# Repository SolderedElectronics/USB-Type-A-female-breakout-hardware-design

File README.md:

# USB Type A female breakout Hardware Design

## About the Product

|  |
| :----------------------------------------------------------: |
| [Buy USB Type A female breakout](https://www.solde.red/333132) |

The USB Type-A connection is still prevalent. If it’s in the electronic devices everywhere around us, it is only natural that we’d want it in our electronic projects. Adding a USB Type-A connection to your circuit is as easy as pie with this breakout board.

The breakout board breaks the GND, D+, D-, and VUSB pins out to the plated through-holes.

---

## Repository Contents

This repository contains all design files for USB Type A female breakout, organized as follows:

- **`CAD` folder**: Contains KiCAD design files, including:
  - Schematics
  - PCB layout
  - Panel PCB layout
  - Source 3D files in Fusion360, if any
  - All files are sorted by version with a detailed change log.
- **`OUTPUTS` folder**: Includes all production-ready files, such as:
  - Bill of Materials (BOM) and interactive BOM (iBOM)
  - PDF versions of schematics
  - 3D `.step` file of the board
  - 3D-printable models
  - Gerber files for PCB manufacturing
  - Image of the pinout of the board
  - Product image
  - Compliance, legal and generic sales documents

Refer to the `Change Log` in the CAD folder for details about updates between versions.

---

## Learn More About the Product

Beyond the repository, explore the following resources:

### Soldered Verify

The **Soldered Verify** system ensures every board you purchase from Soldered is fully functional. It also provides access to exclusive test data for your product. To get started, find the unique Soldered Verify ID on your product's packaging and enter the ID on the [Soldered Verify page](https://soldered.com/verify/) to access test results and additional product details.

### Soldered Community

Soldered Community is your go-to place for technical support. Our engineers track and answer all questions posted there, and it’s a great space for the maker community. Get answers to your questions and solutions for your challenges at [Soldered Community](https://soldered.com/community).

### solde.red

solde.red is an ultimate URL shortener and information hub. Access it by typing solde.red/ followed by your product SKU, e.g., [solde.red/333000](https://solde.red/333000), to find getting-started guides, datasheets, open-source hardware and software files, certifications, images, pinouts, and more. Read more about the shortener [here](https://solde.red/info/).

---

## Contributing

Contributions are welcome! Here’s how you can get involved:

- Submit pull requests to enhance the design or fix issues.
- Report bugs or problems by opening an issue.

We encourage community collaboration to make this product even better.

---

## About Soldered

[Soldered for Makers](https://soldered.com) specializes in designing and manufacturing electronic products tailored for enthusiasts, ranging from hobbyists to professionals. Our portfolio includes electronic boards, sensors, and actuators that are widely utilized in fields such as microelectronics, mechatronics, robotics, programming, and IoT. Every product we offer is designed in-house and built upon open-source hardware and software platforms. Proudly certified and manufactured within the European Union, our catalog likely includes the product you need for your project.

We complement these products with comprehensive tutorials and manuals, product descriptions, schematics, programming codes, and project examples. Our round-the-clock [customer and technical support](https://soldered.com/community) is available for all our products, irrespective of the sales channel. Soldered’s success and services reflect our maker community’s unwavering [trust](https://www.trustpilot.com/review/soldered.com), for which we are deeply grateful. Join our community and create using Soldered products.

---

## License

All Soldered open-source hardware (OSH) is under The TAPR Open Hardware License. Read more in the LICENSE file located in this repository.

**Disclaimer:**

No warranty - all designs in this repository are distributed in the hope that they will be useful, but without any warranty. They are provided "AS IS", therefore without warranty of any kind, either expressed or implied. The entire quality and performance of what you do with the contents of this repository are your responsibility. In no event Soldered Electronics will be liable for your damages, or losses, including any general, special, incidental, or consequential damage arising out of the use or inability to use the contents of this repository. 

---

## Have fun!

Thank you for your support from your fellow makers at Soldered Electronics.

Happy Making!

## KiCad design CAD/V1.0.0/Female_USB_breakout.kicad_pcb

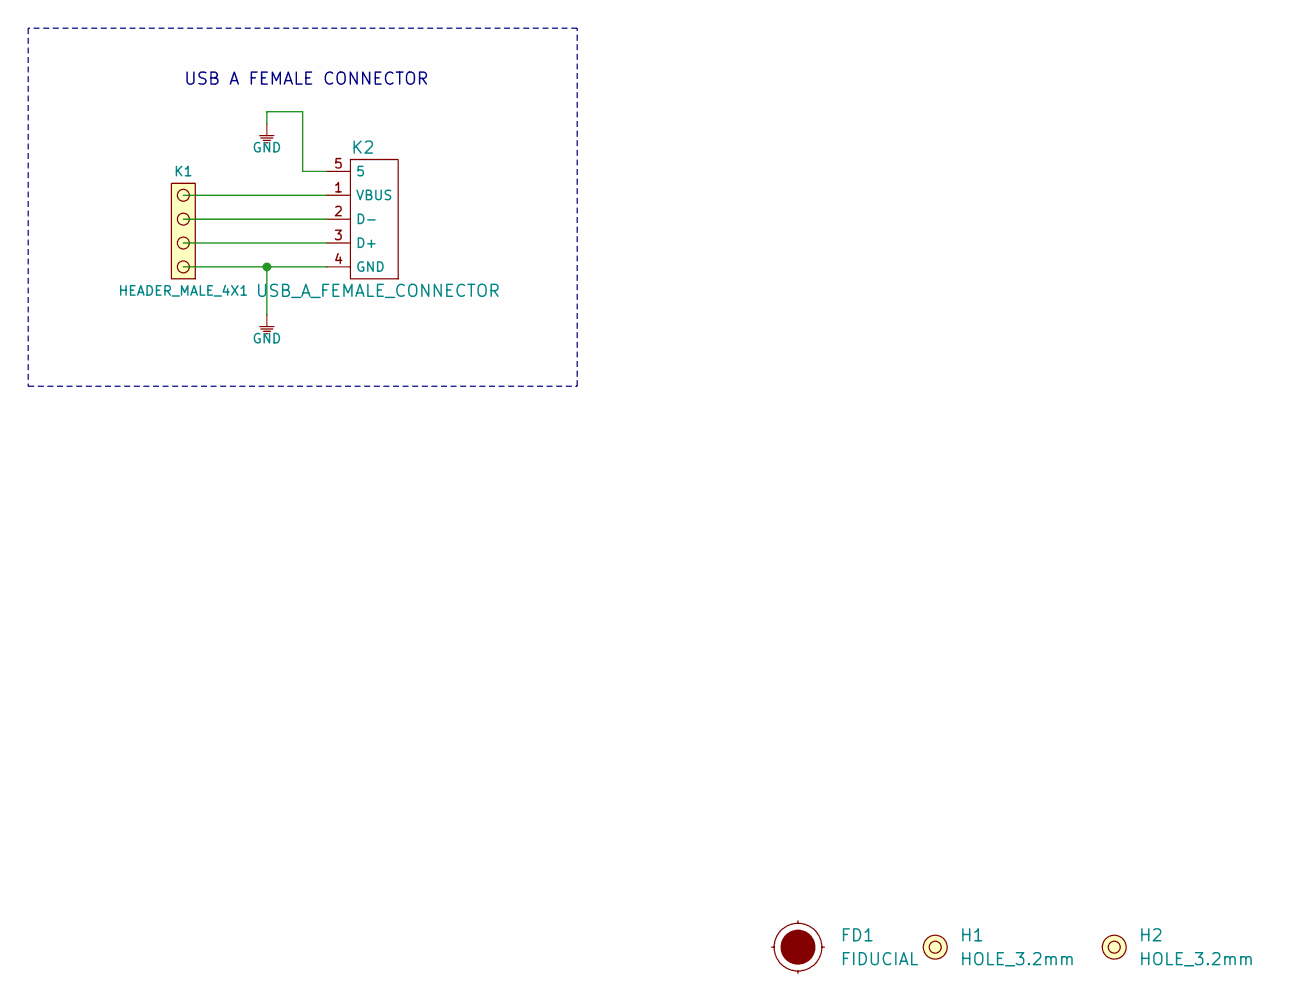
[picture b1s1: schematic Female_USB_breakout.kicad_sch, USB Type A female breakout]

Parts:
FD1: FIDUCIAL; FIDUCIAL_23
H1, H2: HOLE_3.2mm
K1: HEADER_MALE_4X1
K2: USB_A_FEMALE_CONNECTOR; USB_A_FEMALE_CONECTOR

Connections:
GND: K1.1, K2.4 (GND), K2.5
unnamed: K1.2, K2.3 (D+)
unnamed: K1.3, K2.2 (D-)
unnamed: K1.4, K2.1 (VBUS)

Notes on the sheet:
USB A FEMALE CONNECTOR

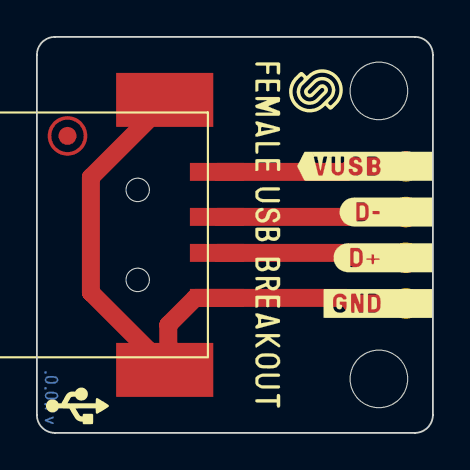
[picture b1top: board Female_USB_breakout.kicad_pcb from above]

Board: 2 copper layers, 22.0 x 22.0 mm, 5 parts (1 on the bottom side), 4 nets.

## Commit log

2022-08-06 Updating open source files.
